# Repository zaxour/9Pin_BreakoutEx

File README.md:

# 9Pin_BreakoutEx
Breakout board for 9 pin mini DIN connectors with additional features for audio and sync.

Leaving the jumpers un-bridged and components empty means the board will act like a standard 9 pin breakout DIN.

If attaching to a system that doesn't have composite and only has a 5V TTL level sync, use the following BOM:

C1: 220uF 6.3V Tantalum 3528 size capacitor
R1: 620 Ohm 1/8W 0603 size Resistor
R2: 86.6 Ohm 1/8 0603 size Resistor

RGB mods for older consoles tend to make the user decide between Composite Video level sync or TTL sync. With this breakout, simply install the resistors and capacitor (value indicated on bottom silkscreen) and use the TTL sync from the RGB modification. This will simultaneously deliver a proper sync voltage to the Composite Video pin on the DIN for using HD Retrovision cables. ***ENSURE THE RGB MOD CAN DRIVE TWO 75 OHM LOADS (Such as THS7374, THS7314 or similar) ***

The solder jumper for audio can be used as follows:
-Right: Connects Right and Left audio nodes, passes to both pins.
-Left: Connects Right audio to the Mono pin

Both jumpers can be soldered to make sure a mono audio signal goes to all of the audio pins.

Top

Bottom

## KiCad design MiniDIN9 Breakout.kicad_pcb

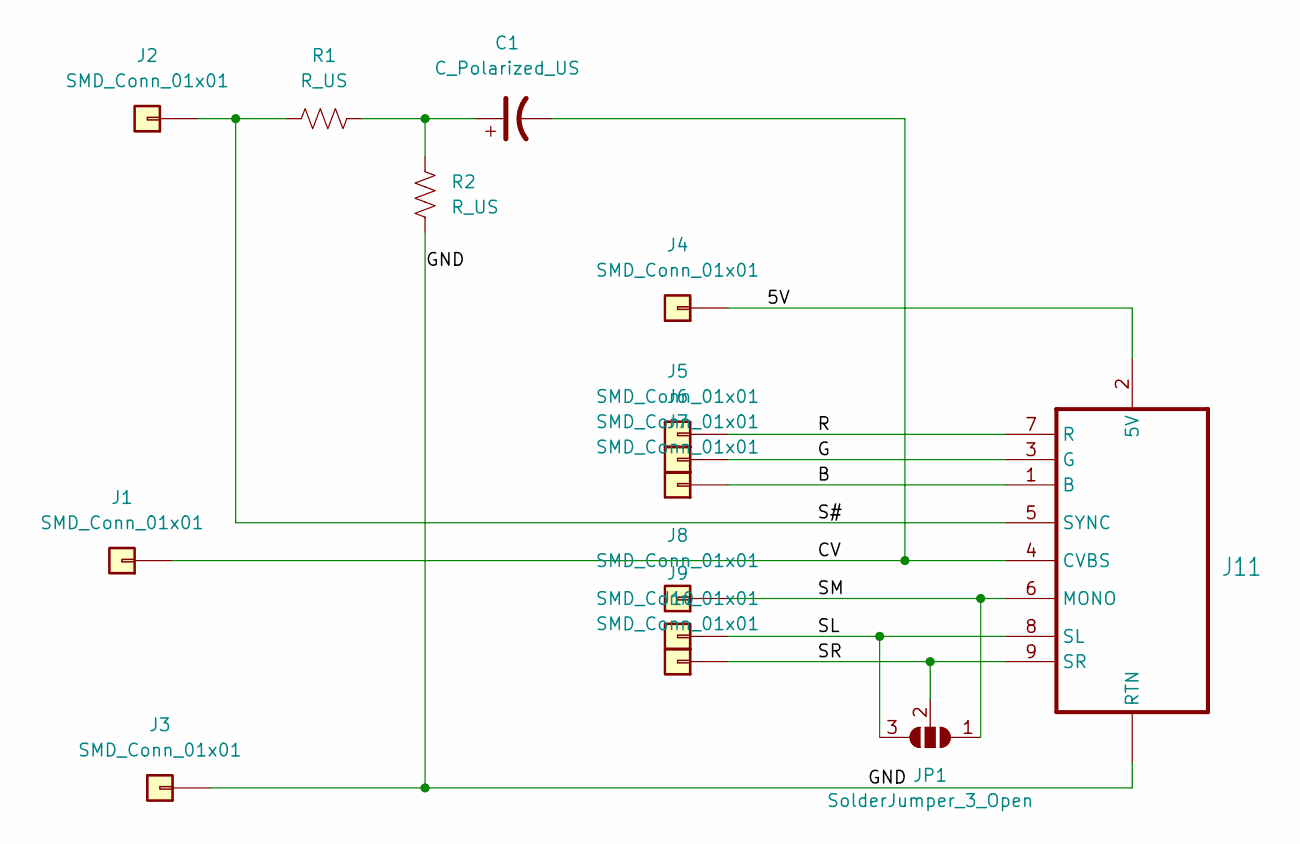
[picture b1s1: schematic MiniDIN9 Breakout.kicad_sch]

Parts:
C1: C_Polarized_US
J1, J2, J3, J4, J5, J6, J7, J8, J9, J10: SMD_Conn_01x01; SolderWirePad_1x01_SMD_1x2mm
J11: MD-90SM_MD2; CUI_MD-90SM
JP1: SolderJumper_3_Open; SolderJumper-3_P2.0mm_Open_TrianglePad1.0x1.5mm
R1, R2: R_US

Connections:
/5V: J4.1, J11.2 (5V)
/B: J7.1, J11.1 (B)
/CV: C1.2, J1.1, J11.4 (CVBS)
/G: J6.1, J11.3 (G)
/GND: J3.1, J11.S1 (RTN), J11.S2 (RTN), J11.S3 (RTN), R2.1
/R: J5.1, J11.7 (R)
/S#: J2.1, J11.5 (SYNC), R1.1
/SL: J9.1, J11.8 (SL), JP1.3 (B)
/SM: J8.1, J11.6 (MONO), JP1.1 (A)
/SR: J10.1, J11.9 (SR), JP1.2 (C)
unnamed: C1.1, R1.2, R2.2

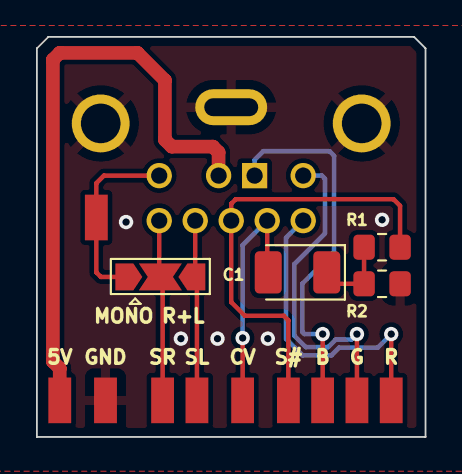
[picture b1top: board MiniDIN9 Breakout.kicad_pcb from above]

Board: 2 copper layers, 21.6 x 22.2 mm, 15 parts (1 on the bottom side), 11 nets.

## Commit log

2022-12-01 Add photos
2022-12-01 README update
